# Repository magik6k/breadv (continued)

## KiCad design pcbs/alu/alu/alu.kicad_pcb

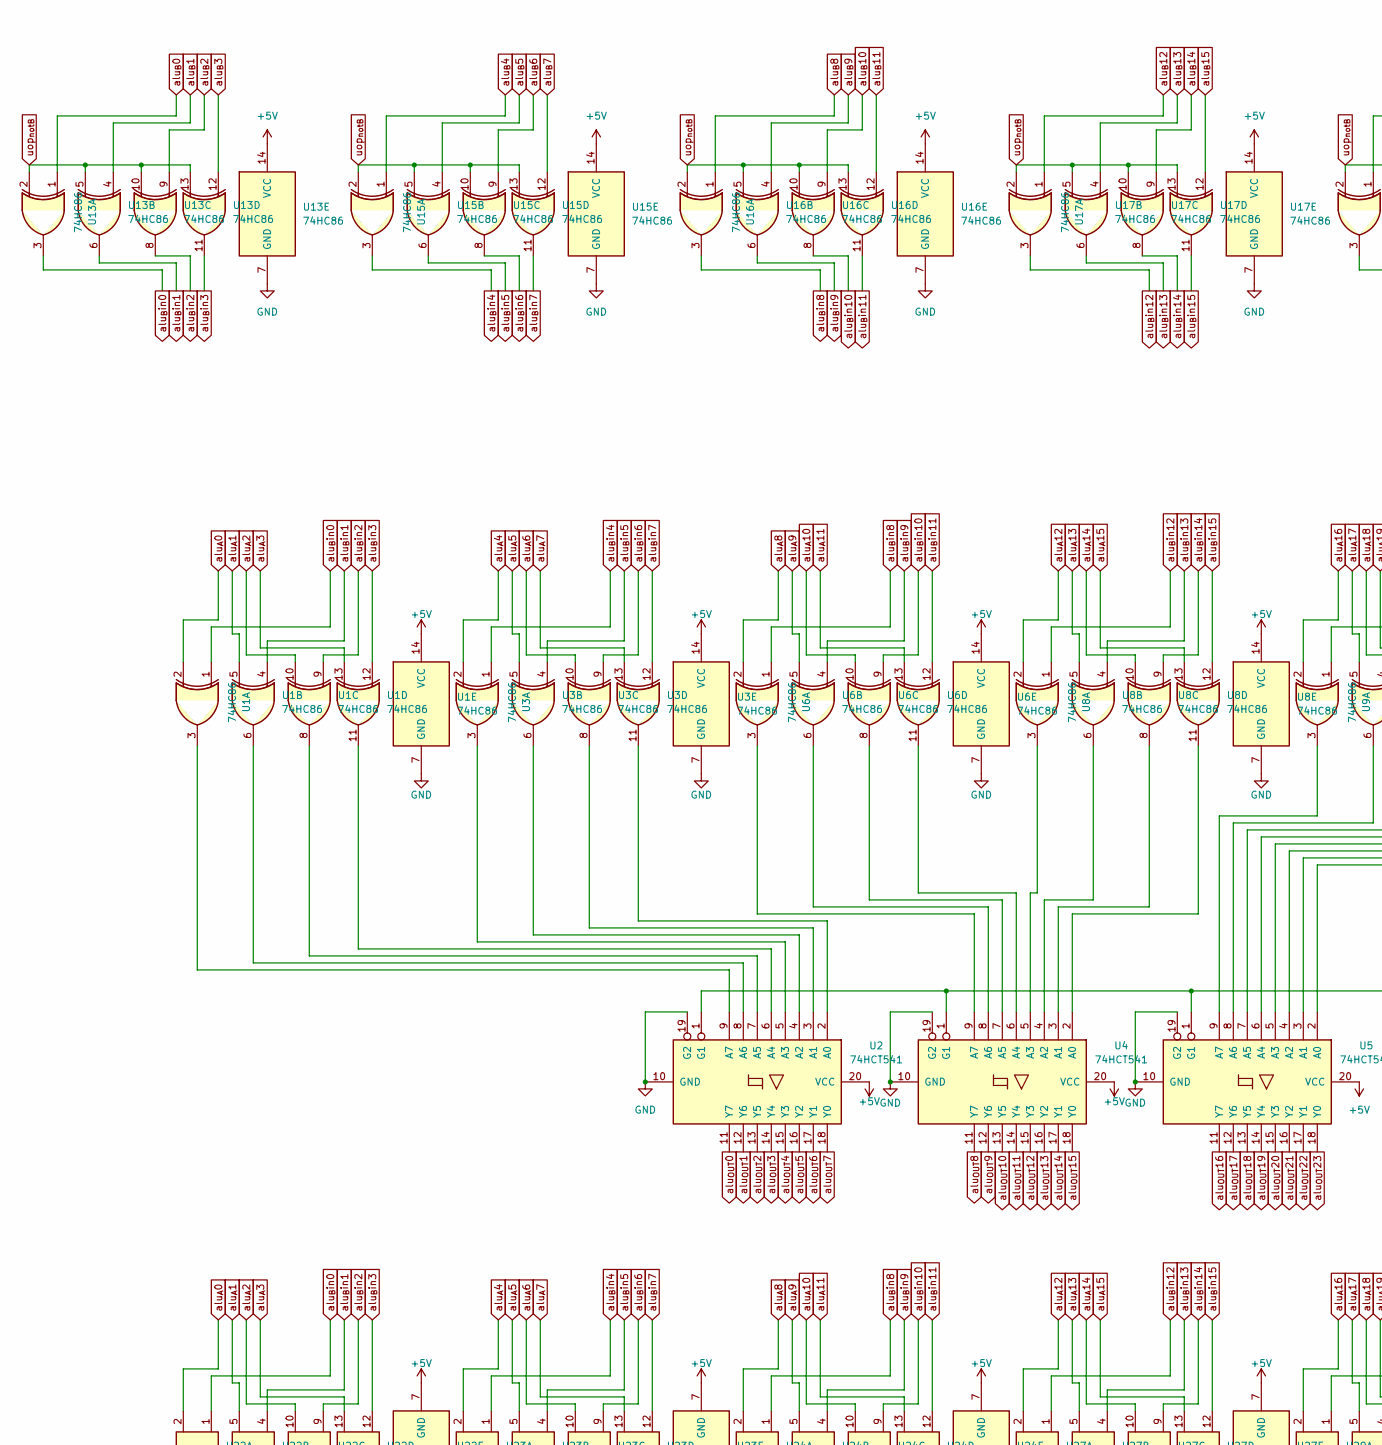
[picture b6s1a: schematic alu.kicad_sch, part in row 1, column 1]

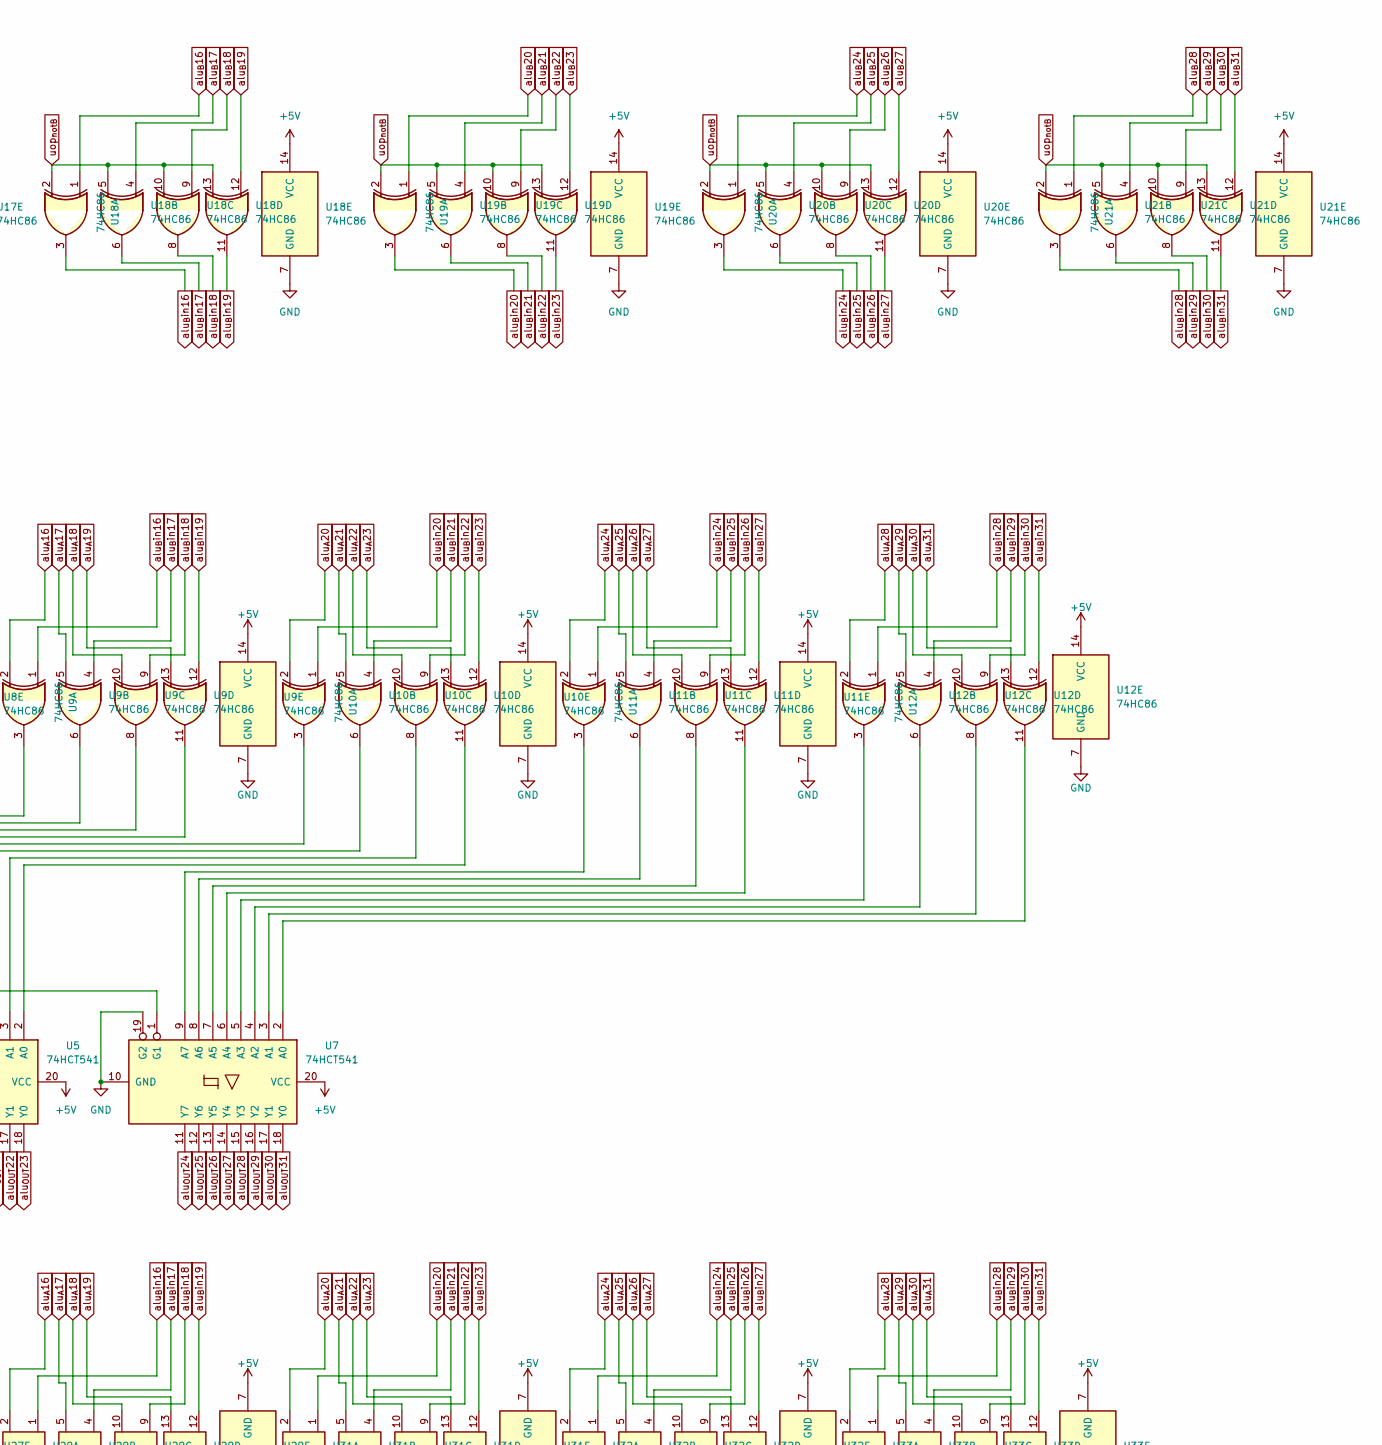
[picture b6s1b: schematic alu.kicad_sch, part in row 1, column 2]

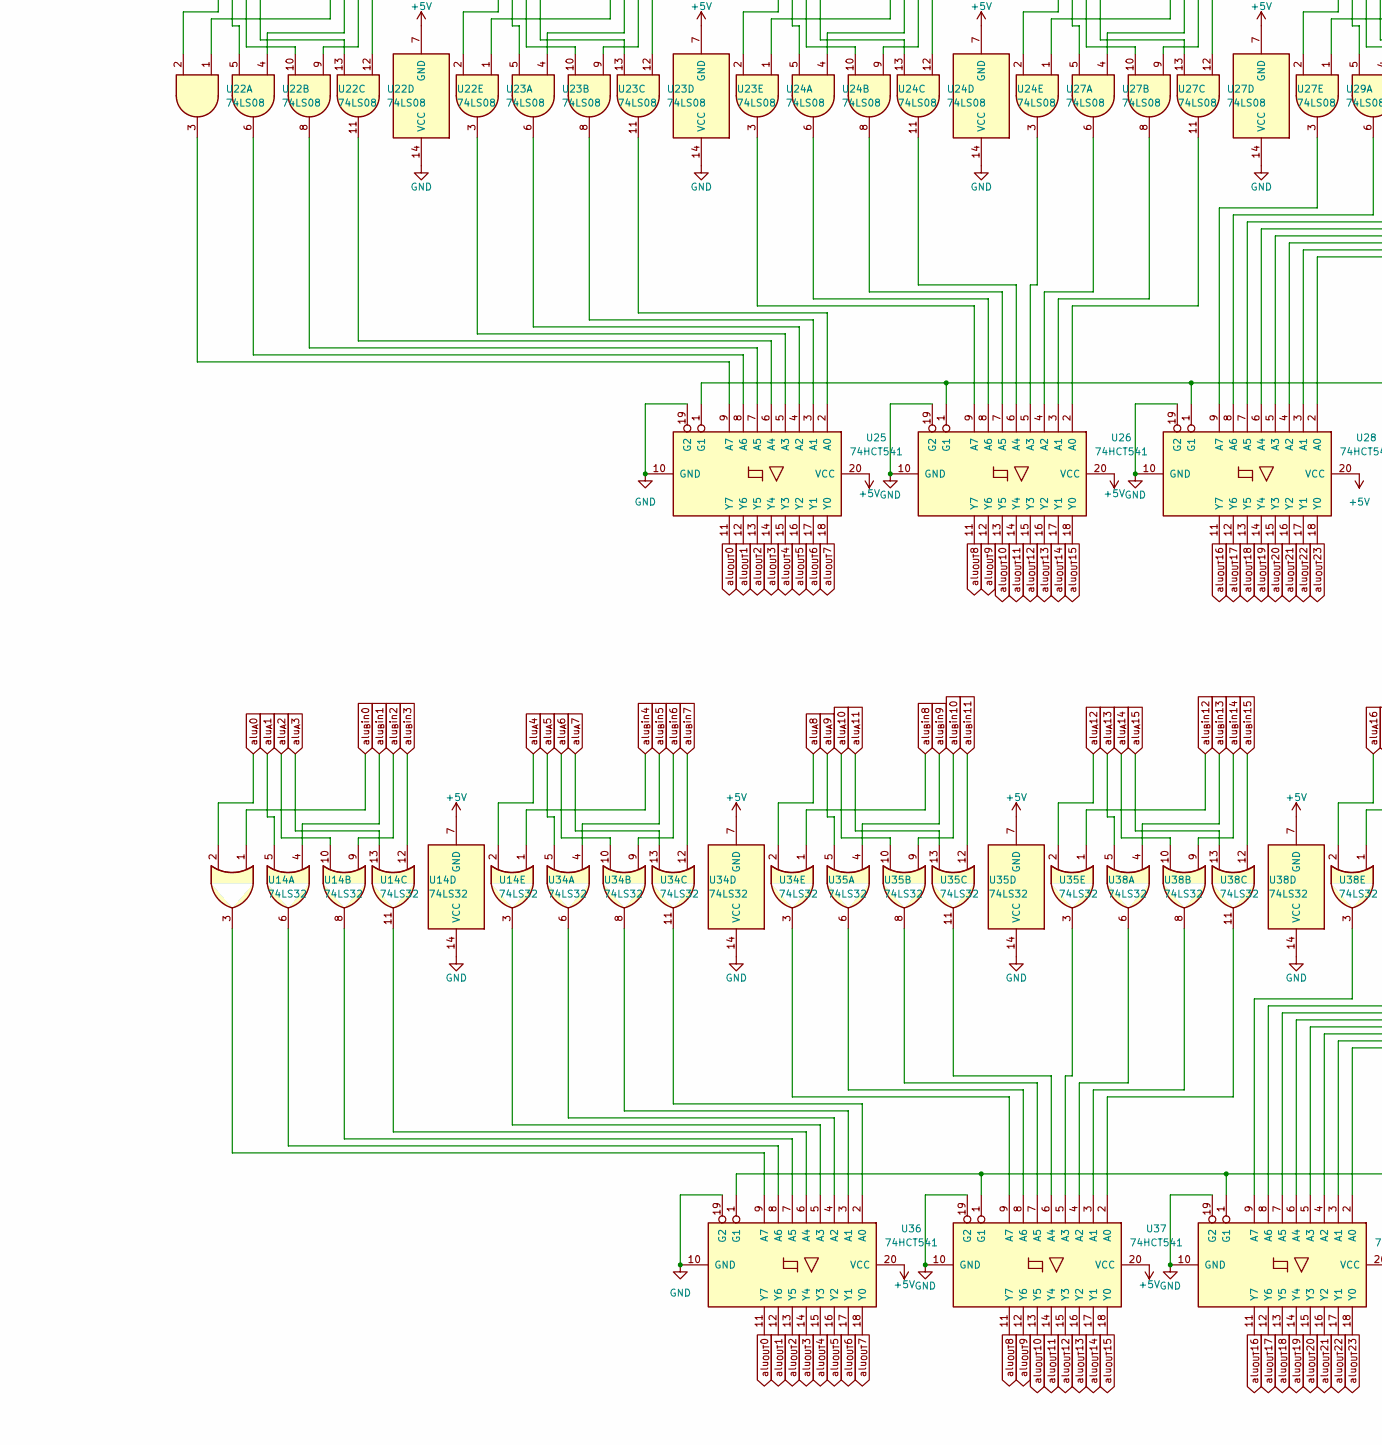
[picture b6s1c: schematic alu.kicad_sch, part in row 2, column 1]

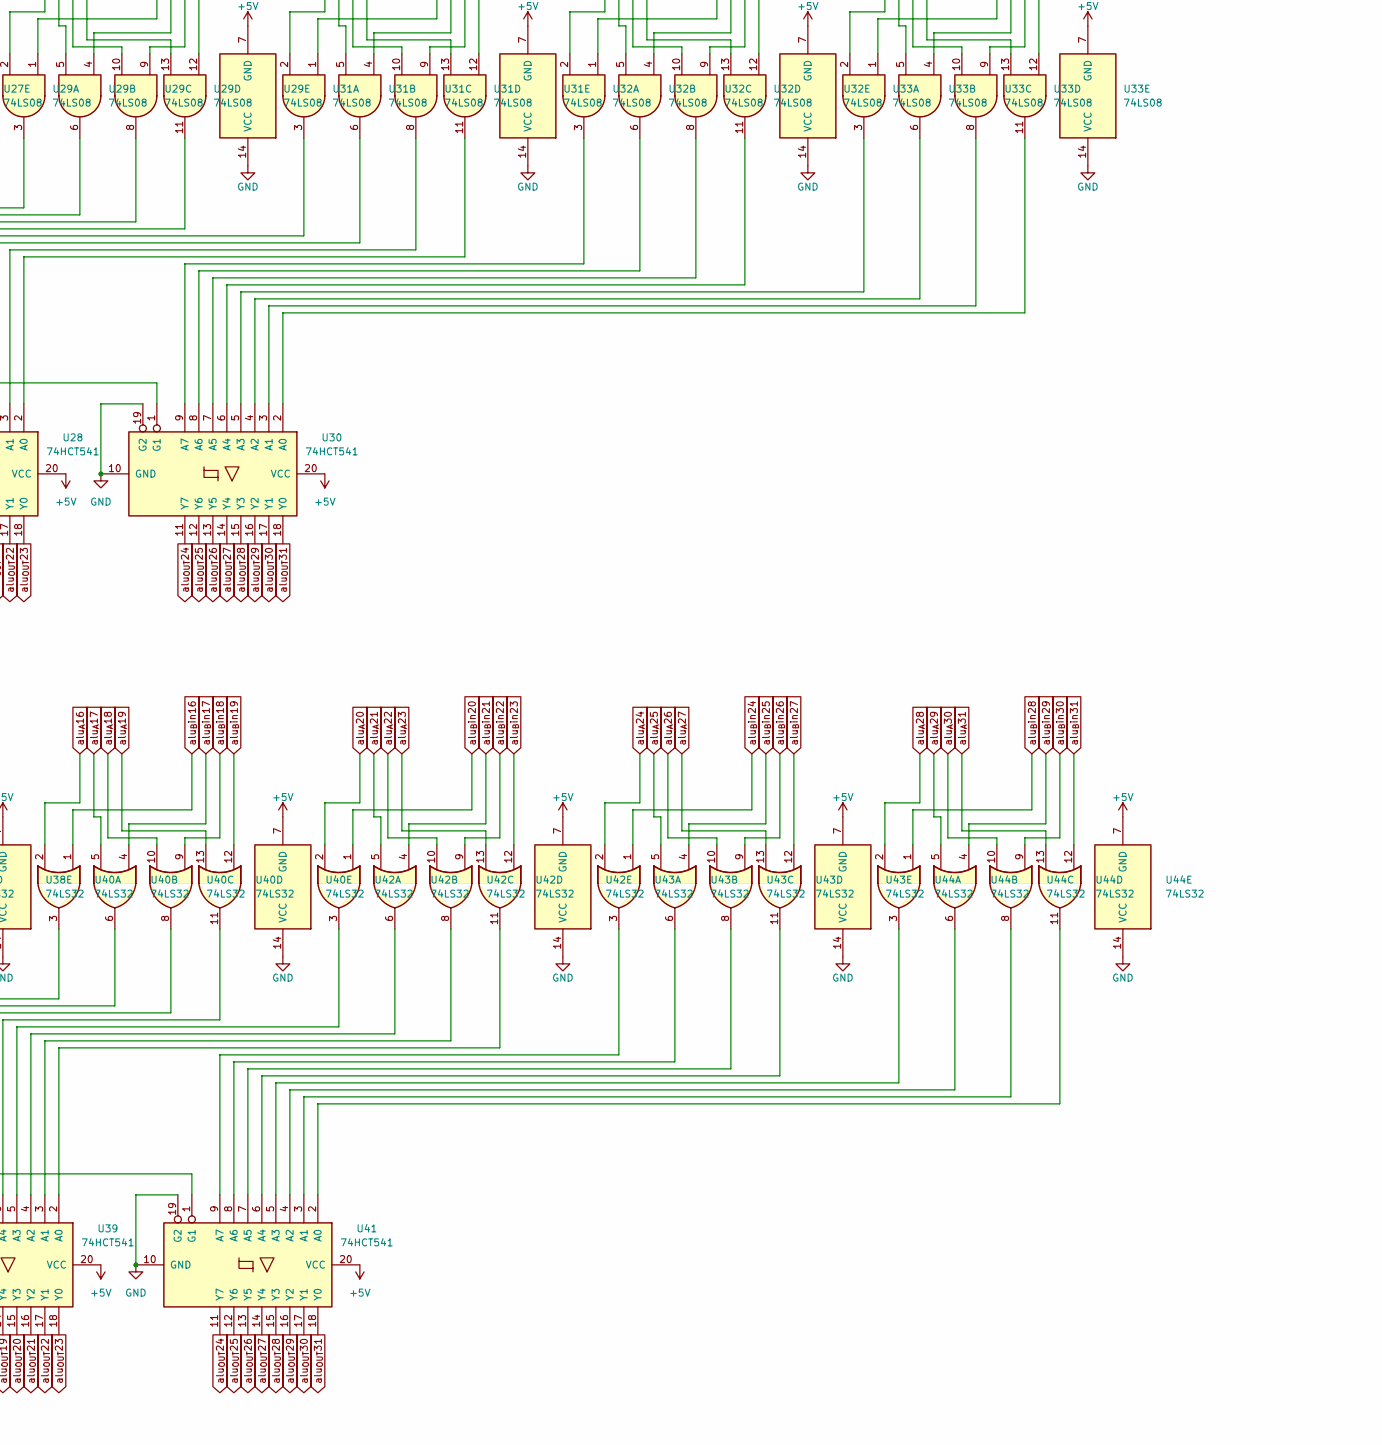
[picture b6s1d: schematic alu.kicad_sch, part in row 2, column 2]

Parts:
U1, U3, U6, U8, U9, U10, U11, U12, U13, U15, U16, U17, U18, U19, U20, U21: 74HC86; DIP-14_W7.62mm_Socket
U2, U4, U5, U7, U25, U26, U28, U30, U36, U37, U39, U41: 74HCT541; DIP-20_W7.62mm_Socket_LongPads
U14, U34, U35, U38, U40, U42, U43, U44: 74LS32; DIP-14_W7.62mm_Socket
U22, U23, U24, U27, U29, U31, U32, U33: 74LS08; DIP-14_W7.62mm_Socket

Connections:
+5V: U1.14 (VCC), U2.20 (VCC), U3.14 (VCC), U4.20 (VCC), U5.20 (VCC), U6.14 (VCC), U7.20 (VCC), U8.14 (VCC), U9.14 (VCC), U10.14 (VCC), U11.14 (VCC), U12.14 (VCC), U13.14 (VCC), U14.7 (GND), U15.14 (VCC), U16.14 (VCC), U17.14 (VCC), U18.14 (VCC), U19.14 (VCC), U20.14 (VCC), U21.14 (VCC), U22.7 (GND), U23.7 (GND), U24.7 (GND), U25.20 (VCC), U26.20 (VCC), U27.7 (GND), U28.20 (VCC), U29.7 (GND), U30.20 (VCC), U31.7 (GND), U32.7 (GND), U33.7 (GND), U34.7 (GND), U35.7 (GND), U36.20 (VCC), U37.20 (VCC), U38.7 (GND), U39.20 (VCC), U40.7 (GND), U41.20 (VCC), U42.7 (GND), U43.7 (GND), U44.7 (GND)
GND: U1.7 (GND), U2.10 (GND), U2.19 (G2), U3.7 (GND), U4.10 (GND), U4.19 (G2), U5.10 (GND), U5.19 (G2), U6.7 (GND), U7.10 (GND), U7.19 (G2), U8.7 (GND), U9.7 (GND), U10.7 (GND), U11.7 (GND), U12.7 (GND), U13.7 (GND), U14.14 (VCC), U15.7 (GND), U16.7 (GND), U17.7 (GND), U18.7 (GND), U19.7 (GND), U20.7 (GND), U21.7 (GND), U22.14 (VCC), U23.14 (VCC), U24.14 (VCC), U25.10 (GND), U25.19 (G2), U26.10 (GND), U26.19 (G2), U27.14 (VCC), U28.10 (GND), U28.19 (G2), U29.14 (VCC), U30.10 (GND), U30.19 (G2), U31.14 (VCC), U32.14 (VCC), U33.14 (VCC), U34.14 (VCC), U35.14 (VCC), U36.10 (GND), U36.19 (G2), U37.10 (GND), U37.19 (G2), U38.14 (VCC), U39.10 (GND), U39.19 (G2), U40.14 (VCC), U41.10 (GND), U41.19 (G2), U42.14 (VCC), U43.14 (VCC), U44.14 (VCC)
unnamed: U1.3, U2.9 (A7)
unnamed: U1.6, U2.8 (A6)
unnamed: U1.8, U2.7 (A5)
unnamed: U1.11, U2.6 (A4)
unnamed: U2.2 (A0), U3.11
unnamed: U2.3 (A1), U3.8
unnamed: U2.4 (A2), U3.6
unnamed: U2.5 (A3), U3.3
unnamed: U4.2 (A0), U8.11
unnamed: U4.3 (A1), U8.8
unnamed: U4.4 (A2), U8.6
unnamed: U4.5 (A3), U8.3
unnamed: U4.6 (A4), U6.11
unnamed: U4.7 (A5), U6.8
unnamed: U4.8 (A6), U6.6
unnamed: U4.9 (A7), U6.3
unnamed: U5.2 (A0), U10.11
unnamed: U5.3 (A1), U10.8
unnamed: U5.4 (A2), U10.6
unnamed: U5.5 (A3), U10.3
unnamed: U5.6 (A4), U9.11
unnamed: U5.7 (A5), U9.8
unnamed: U5.8 (A6), U9.6
unnamed: U5.9 (A7), U9.3
unnamed: U2.1 (G1), U4.1 (G1), U5.1 (G1), U7.1 (G1)
unnamed: U7.2 (A0), U12.11
unnamed: U7.3 (A1), U12.8
unnamed: U7.4 (A2), U12.6
unnamed: U7.5 (A3), U12.3
unnamed: U7.6 (A4), U11.11
unnamed: U7.7 (A5), U11.8
unnamed: U7.8 (A6), U11.6
unnamed: U7.9 (A7), U11.3
unnamed: U14.3, U36.9 (A7)
unnamed: U14.6, U36.8 (A6)
unnamed: U14.8, U36.7 (A5)
unnamed: U14.11, U36.6 (A4)
unnamed: U22.3, U25.9 (A7)
unnamed: U22.6, U25.8 (A6)
unnamed: U22.8, U25.7 (A5)
unnamed: U22.11, U25.6 (A4)
unnamed: U23.3, U25.5 (A3)
unnamed: U23.6, U25.4 (A2)
unnamed: U23.8, U25.3 (A1)
unnamed: U23.11, U25.2 (A0)
unnamed: U24.3, U26.9 (A7)
unnamed: U24.6, U26.8 (A6)
unnamed: U24.8, U26.7 (A5)
unnamed: U24.11, U26.6 (A4)
unnamed: U25.1 (G1), U26.1 (G1), U28.1 (G1), U30.1 (G1)
unnamed: U26.2 (A0), U27.11
unnamed: U26.3 (A1), U27.8
unnamed: U26.4 (A2), U27.6
unnamed: U26.5 (A3), U27.3
unnamed: U28.2 (A0), U31.11
unnamed: U28.3 (A1), U31.8
unnamed: U28.4 (A2), U31.6
unnamed: U28.5 (A3), U31.3
unnamed: U28.6 (A4), U29.11
unnamed: U28.7 (A5), U29.8
unnamed: U28.8 (A6), U29.6
unnamed: U28.9 (A7), U29.3
unnamed: U30.2 (A0), U33.11
unnamed: U30.3 (A1), U33.8
unnamed: U30.4 (A2), U33.6
unnamed: U30.5 (A3), U33.3
unnamed: U30.6 (A4), U32.11
unnamed: U30.7 (A5), U32.8
unnamed: U30.8 (A6), U32.6
unnamed: U30.9 (A7), U32.3
unnamed: U34.3, U36.5 (A3)
unnamed: U34.6, U36.4 (A2)
unnamed: U34.8, U36.3 (A1)
unnamed: U34.11, U36.2 (A0)
unnamed: U35.3, U37.9 (A7)
unnamed: U35.6, U37.8 (A6)
unnamed: U35.8, U37.7 (A5)
unnamed: U35.11, U37.6 (A4)
unnamed: U36.1 (G1), U37.1 (G1), U39.1 (G1), U41.1 (G1)
unnamed: U37.2 (A0), U38.11
unnamed: U37.3 (A1), U38.8
unnamed: U37.4 (A2), U38.6
unnamed: U37.5 (A3), U38.3
unnamed: U39.2 (A0), U42.11
unnamed: U39.3 (A1), U42.8
unnamed: U39.4 (A2), U42.6
unnamed: U39.5 (A3), U42.3
unnamed: U39.6 (A4), U40.11
unnamed: U39.7 (A5), U40.8
unnamed: U39.8 (A6), U40.6
unnamed: U39.9 (A7), U40.3
unnamed: U41.2 (A0), U44.11
unnamed: U41.3 (A1), U44.8
unnamed: U41.4 (A2), U44.6
unnamed: U41.5 (A3), U44.3
unnamed: U41.6 (A4), U43.11
unnamed: U41.7 (A5), U43.8
unnamed: U41.8 (A6), U43.6
unnamed: U41.9 (A7), U43.3
alu_{A}0: U1.2, U14.2, U22.2
alu_{A}1: U1.5, U14.5, U22.5
alu_{A}2: U1.10, U14.10, U22.10
alu_{A}3: U1.13, U14.13, U22.13
alu_{A}4: U3.2, U23.2, U34.2
alu_{A}5: U3.5, U23.5, U34.5
alu_{A}6: U3.10, U23.10, U34.10
alu_{A}7: U3.13, U23.13, U34.13
alu_{A}8: U6.2, U24.2, U35.2
alu_{A}9: U6.5, U24.5, U35.5
alu_{A}10: U6.10, U24.10, U35.10
alu_{A}11: U6.13, U24.13, U35.13
alu_{A}12: U8.2, U27.2, U38.2
alu_{A}13: U8.5, U27.5, U38.5
alu_{A}14: U8.10, U27.10, U38.10
alu_{A}15: U8.13, U27.13, U38.13
alu_{A}16: U9.2, U29.2, U40.2
alu_{A}17: U9.5, U29.5, U40.5
alu_{A}18: U9.10, U29.10, U40.10
alu_{A}19: U9.13, U29.13, U40.13
alu_{A}20: U10.2, U31.2, U42.2
alu_{A}21: U10.5, U31.5, U42.5
alu_{A}22: U10.10, U31.10, U42.10
alu_{A}23: U10.13, U31.13, U42.13
alu_{A}24: U11.2, U32.2, U43.2
alu_{A}25: U11.5, U32.5, U43.5
alu_{A}26: U11.10, U32.10, U43.10
alu_{A}27: U11.13, U32.13, U43.13
alu_{A}28: U12.2, U33.2, U44.2
alu_{A}29: U12.5, U33.5, U44.5
alu_{A}30: U12.10, U33.10, U44.10
alu_{A}31: U12.13, U33.13, U44.13
alu_{B}0: U13.1
alu_{B}1: U13.4
alu_{B}2: U13.9
alu_{B}3: U13.12
alu_{B}4: U15.1
alu_{B}5: U15.4
alu_{B}6: U15.9
alu_{B}7: U15.12
alu_{B}8: U16.1
alu_{B}9: U16.4
alu_{B}10: U16.9
alu_{B}11: U16.12
alu_{B}12: U17.1
alu_{B}13: U17.4
alu_{B}14: U17.9
alu_{B}15: U17.12
alu_{B}16: U18.1
alu_{B}17: U18.4
alu_{B}18: U18.9
alu_{B}19: U18.12
alu_{B}20: U19.1
alu_{B}21: U19.4
alu_{B}22: U19.9
alu_{B}23: U19.12
alu_{B}24: U20.1
alu_{B}25: U20.4
alu_{B}26: U20.9
alu_{B}27: U20.12
alu_{B}28: U21.1
alu_{B}29: U21.4
alu_{B}30: U21.9
alu_{B}31: U21.12
alu_{B}in0: U1.1, U13.3, U14.1, U22.1
alu_{B}in1: U1.4, U13.6, U14.4, U22.4
alu_{B}in2: U1.9, U13.8, U14.9, U22.9
alu_{B}in3: U1.12, U13.11, U14.12, U22.12
alu_{B}in4: U3.1, U15.3, U23.1, U34.1
alu_{B}in5: U3.4, U15.6, U23.4, U34.4
alu_{B}in6: U3.9, U15.8, U23.9, U34.9
alu_{B}in7: U3.12, U15.11, U23.12, U34.12
alu_{B}in8: U6.1, U16.3, U24.1, U35.1
alu_{B}in9: U6.4, U16.6, U24.4, U35.4
alu_{B}in10: U6.9, U16.8, U24.9, U35.9
alu_{B}in11: U6.12, U16.11, U24.12, U35.12
alu_{B}in12: U8.1, U17.3, U27.1, U38.1
alu_{B}in13: U8.4, U17.6, U27.4, U38.4
alu_{B}in14: U8.9, U17.8, U27.9, U38.9
alu_{B}in15: U8.12, U17.11, U27.12, U38.12
alu_{B}in16: U9.1, U18.3, U29.1, U40.1
alu_{B}in17: U9.4, U18.6, U29.4, U40.4
alu_{B}in18: U9.9, U18.8, U29.9, U40.9
alu_{B}in19: U9.12, U18.11, U29.12, U40.12
alu_{B}in20: U10.1, U19.3, U31.1, U42.1
alu_{B}in21: U10.4, U19.6, U31.4, U42.4
alu_{B}in22: U10.9, U19.8, U31.9, U42.9
alu_{B}in23: U10.12, U19.11, U31.12, U42.12
alu_{B}in24: U11.1, U20.3, U32.1, U43.1
alu_{B}in25: U11.4, U20.6, U32.4, U43.4
alu_{B}in26: U11.9, U20.8, U32.9, U43.9
alu_{B}in27: U11.12, U20.11, U32.12, U43.12
alu_{B}in28: U12.1, U21.3, U33.1, U44.1
alu_{B}in29: U12.4, U21.6, U33.4, U44.4
alu_{B}in30: U12.9, U21.8, U33.9, U44.9
alu_{B}in31: U12.12, U21.11, U33.12, U44.12
alu_{OUT}0: U2.11 (Y7), U25.11 (Y7), U36.11 (Y7)
alu_{OUT}1: U2.12 (Y6), U25.12 (Y6), U36.12 (Y6)
alu_{OUT}2: U2.13 (Y5), U25.13 (Y5), U36.13 (Y5)
alu_{OUT}3: U2.14 (Y4), U25.14 (Y4), U36.14 (Y4)
alu_{OUT}4: U2.15 (Y3), U25.15 (Y3), U36.15 (Y3)
alu_{OUT}5: U2.16 (Y2), U25.16 (Y2), U36.16 (Y2)
alu_{OUT}6: U2.17 (Y1), U25.17 (Y1), U36.17 (Y1)
alu_{OUT}7: U2.18 (Y0), U25.18 (Y0), U36.18 (Y0)
alu_{OUT}8: U4.11 (Y7), U26.11 (Y7), U37.11 (Y7)
alu_{OUT}9: U4.12 (Y6), U26.12 (Y6), U37.12 (Y6)
alu_{OUT}10: U4.13 (Y5), U26.13 (Y5), U37.13 (Y5)
alu_{OUT}11: U4.14 (Y4), U26.14 (Y4), U37.14 (Y4)
alu_{OUT}12: U4.15 (Y3), U26.15 (Y3), U37.15 (Y3)
alu_{OUT}13: U4.16 (Y2), U26.16 (Y2), U37.16 (Y2)
alu_{OUT}14: U4.17 (Y1), U26.17 (Y1), U37.17 (Y1)
alu_{OUT}15: U4.18 (Y0), U26.18 (Y0), U37.18 (Y0)
alu_{OUT}16: U5.11 (Y7), U28.11 (Y7), U39.11 (Y7)
alu_{OUT}17: U5.12 (Y6), U28.12 (Y6), U39.12 (Y6)
alu_{OUT}18: U5.13 (Y5), U28.13 (Y5), U39.13 (Y5)
alu_{OUT}19: U5.14 (Y4), U28.14 (Y4), U39.14 (Y4)
alu_{OUT}20: U5.15 (Y3), U28.15 (Y3), U39.15 (Y3)
alu_{OUT}21: U5.16 (Y2), U28.16 (Y2), U39.16 (Y2)
alu_{OUT}22: U5.17 (Y1), U28.17 (Y1), U39.17 (Y1)
alu_{OUT}23: U5.18 (Y0), U28.18 (Y0), U39.18 (Y0)
alu_{OUT}24: U7.11 (Y7), U30.11 (Y7), U41.11 (Y7)
alu_{OUT}25: U7.12 (Y6), U30.12 (Y6), U41.12 (Y6)
alu_{OUT}26: U7.13 (Y5), U30.13 (Y5), U41.13 (Y5)
alu_{OUT}27: U7.14 (Y4), U30.14 (Y4), U41.14 (Y4)
alu_{OUT}28: U7.15 (Y3), U30.15 (Y3), U41.15 (Y3)
alu_{OUT}29: U7.16 (Y2), U30.16 (Y2), U41.16 (Y2)
alu_{OUT}30: U7.17 (Y1), U30.17 (Y1), U41.17 (Y1)
alu_{OUT}31: U7.18 (Y0), U30.18 (Y0), U41.18 (Y0)
uop_{notB}: U13.2, U13.5, U13.10, U13.13, U15.2, U15.5, U15.10, U15.13, U16.2, U16.5, U16.10, U16.13, U17.2, U17.5, U17.10, U17.13, U18.2, U18.5, U18.10, U18.13, U19.2, U19.5, U19.10, U19.13, U20.2, U20.5, U20.10, U20.13, U21.2, U21.5, U21.10, U21.13

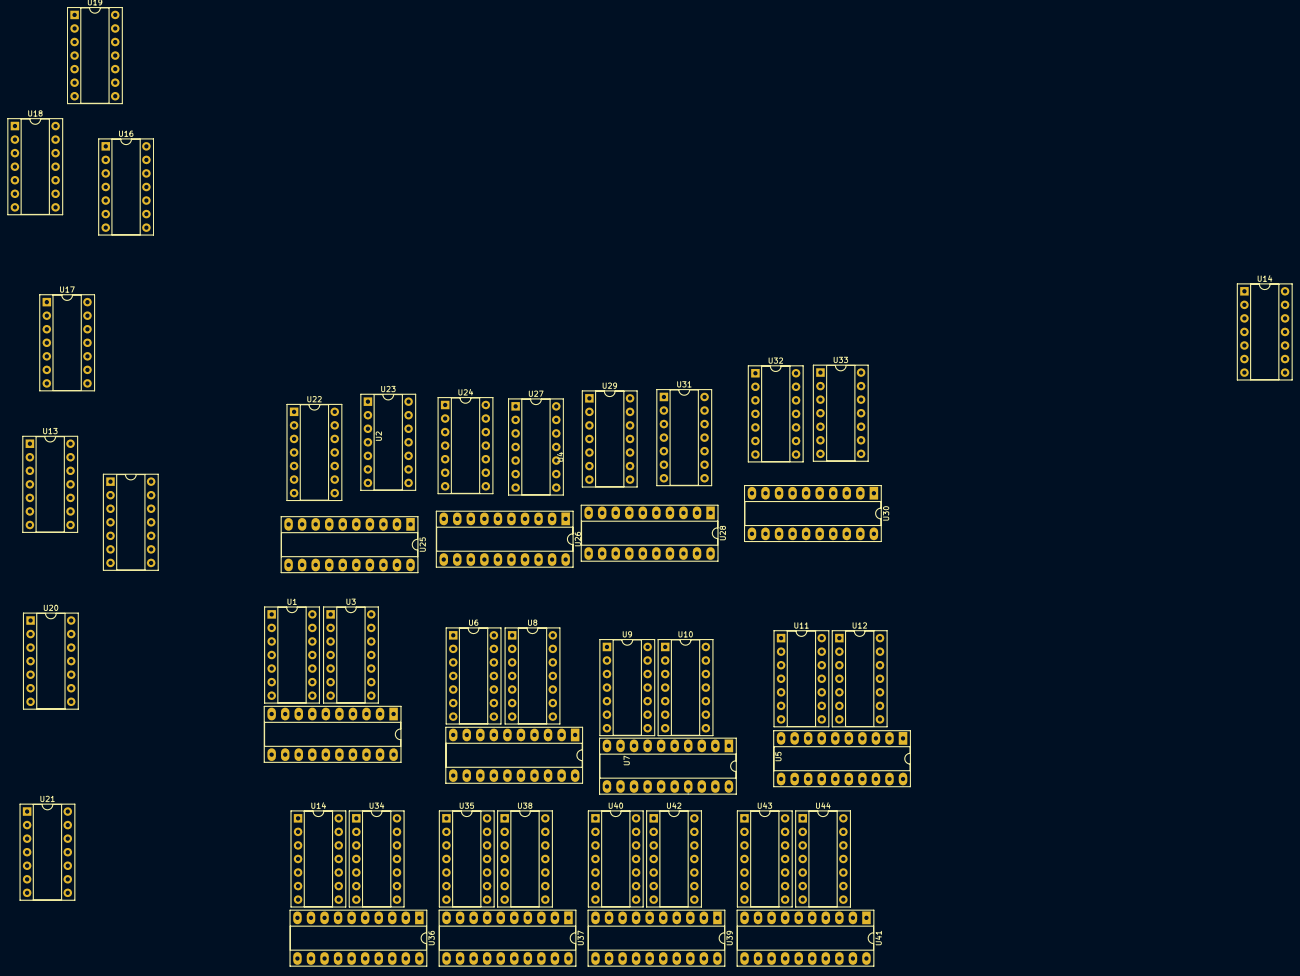
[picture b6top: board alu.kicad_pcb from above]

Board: 2 copper layers, 45 parts (0 on the bottom side), 198 nets.

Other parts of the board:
U14#2: 74LS08; DIP-14_W7.62mm_Socket

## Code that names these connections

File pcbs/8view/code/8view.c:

#include<avr/io.h>
#include<avr/wdt.h>

#define INVERTED 1 // output upside down

#define FILPPED 0 // displays upside down

/*

*A*
F*B
*G*
E*C
*D* DP

*/

#define D1_l1 (1<<PA0)
#define D1_l6 (1<<PA1)
#define D1_l2 (1<<PA2)
#define D1_l7 (1<<PA3)
#define D1_l3 (1<<PA4)
#define D1_l5 (1<<PA5)
#define D1_l8 (1<<PA6)
#define D1_l4 (1<<PA7)

#define D2_l7 (1<<PB0)
#define D2_l8 (1<<PB1)
#define D2_l5 (1<<PB2)
#define D2_l4 (1<<PB3)
#define D2_l6 (1<<PB4)
#define D2_l3 (1<<PB5)
#define D2_l1 (1<<PB6)
#define D2_l2 (1<<PB7)

#if FILPPED
#define D1_real_A D1_l4
#define D1_real_B D1_l5
#define D1_real_C D1_l7
#define D1_real_D D1_l1
#define D1_real_E D1_l2
#define D1_real_F D1_l8
#define D1_real_G D1_l3
#define D1_real_DP D1_l6

#define D2_real_A D2_l4
#define D2_real_B D2_l5
#define D2_real_C D2_l7
#define D2_real_D D2_l1
#define D2_real_E D2_l2
#define D2_real_F D2_l8
#define D2_real_G D2_l3
#define D2_real_DP D2_l6
#else
#define D1_real_A D1_l1
#define D1_real_B D1_l2
#define D1_real_C D1_l3
#define D1_real_D D1_l4
#define D1_real_E D1_l5
#define D1_real_F D1_l6
#define D1_real_G D1_l7
#define D1_real_DP D1_l8

#define D2_real_A D2_l1
#define D2_real_B D2_l2
#define D2_real_C D2_l3
#define D2_real_D D2_l4
#define D2_real_E D2_l5
#define D2_real_F D2_l6
#define D2_real_G D2_l7
#define D2_real_DP D2_l8
#endif

#if INVERTED
#define D1_A D1_real_D
#define D1_B D1_real_E
#define D1_C D1_real_F
#define D1_D D1_real_A
#define D1_E D1_real_B
#define D1_F D1_real_C
#define D1_G D1_real_G
#define D1_DP D1_real_DP

#define D2_A D2_real_D
#define D2_B D2_real_E
#define D2_C D2_real_F
#define D2_D D2_real_A
#define D2_E D2_real_B
#define D2_F D2_real_C
#define D2_G D2_real_G
#define D2_DP D2_real_DP
#else
#define D1_A D1_real_A
#define D1_B D1_real_B
#define D1_C D1_real_C
#define D1_D D1_real_D
#define D1_E D1_real_E
#define D1_F D1_real_F
#define D1_G D1_real_G
#define D1_DP D1_real_DP

#define D2_A D2_real_A
#define D2_B D2_real_B
#define D2_C D2_real_C
#define D2_D D2_real_D
#define D2_E D2_real_E
#define D2_F D2_real_F
#define D2_G D2_real_G
#define D2_DP D2_real_DP
#endif

#define D1_c1 D1_B|D1_C|0
#define D1_c2 D1_A|D1_B|D1_D|D1_E|D1_G|0
#define D1_c3 D1_A|D1_B|D1_C|D1_D|D1_G|0
#define D1_c4 D1_B|D1_C|D1_F|D1_G|0
#define D1_c5 D1_A|D1_C|D1_D|D1_F|D1_G|0
#define D1_c6 D1_A|D1_C|D1_D|D1_E|D1_F|D1_G|0
#define D1_c7 D1_A|D1_B|D1_C|0
#define D1_c8 D1_A|D1_B|D1_C|D1_D|D1_E|D1_F|D1_G|0
#define D1_c9 D1_A|D1_B|D1_C|D1_D|D1_F|D1_G|0
#define D1_c0 D1_A|D1_B|D1_C|D1_D|D1_E|D1_F|0
#define D1_cA D1_A|D1_B|D1_C|D1_D|D1_E|D1_G|0
#define D1_cB D1_C|D1_D|D1_E|D1_F|D1_G|0
#define D1_cC D1_D|D1_E|D1_G|0
#define D1_cD D1_B|D1_C|D1_D|D1_E|D1_G|0
#define D1_cE D1_A|D1_D|D1_E|D1_F|D1_G|0
#define D1_cF D1_A|D1_E|D1_F|D1_G|0
#define D1_cG D1_A|D1_C|D1_D|D1_E|D1_F|0
#define D1_cH D1_C|D1_E|D1_F|D1_G|0
#define D1_cI D1_A|D1_E|0
#define D1_cJ D1_A|D1_C|D1_D|0
#define D1_cK D1_A|D1_C|D1_E|D1_F|D1_G|0
#define D1_cL D1_D|D1_E|D1_F|0
#define D1_cM D1_A|D1_C|D1_E|D1_G|0
#define D1_cN D1_C|D1_E|D1_G|0
#define D1_cO D1_C|D1_D|D1_E|D1_G|0
#define D1_cP D1_A|D1_B|D1_E|D1_F|D1_G|0
#define D1_cQ D1_A|D1_B|D1_C|D1_F|D1_G|0
#define D1_cR D1_E|D1_G|0
#define D1_cS D1_A|D1_C|D1_D|D1_F|0
#define D1_cT D1_D|D1_E|D1_F|D1_G|0
#define D1_cU D1_C|D1_D|D1_E|0
#define D1_cV D1_B|D1_D|D1_F|0
#define D1_cW D1_B|D1_D|D1_F|D1_G|0
#define D1_cX D1_C|D1_E|0
#define D1_cY D1_B|D1_C|D1_D|D1_F|D1_G|0
#define D1_cZ D1_A|D1_B|D1_D|D1_E|0

#define D2_c1 D2_B|D2_C|0
#define D2_c2 D2_A|D2_B|D2_D|D2_E|D2_G|0
#define D2_c3 D2_A|D2_B|D2_C|D2_D|D2_G|0
#define D2_c4 D2_B|D2_C|D2_F|D2_G|0
#define D2_c5 D2_A|D2_C|D2_D|D2_F|D2_G|0
#define D2_c6 D2_A|D2_C|D2_D|D2_E|D2_F|D2_G|0
#define D2_c7 D2_A|D2_B|D2_C|0
#define D2_c8 D2_A|D2_B|D2_C|D2_D|D2_E|D2_F|D2_G|0
#define D2_c9 D2_A|D2_B|D2_C|D2_D|D2_F|D2_G|0
#define D2_c0 D2_A|D2_B|D2_C|D2_D|D2_E|D2_F|0
#define D2_cA D2_A|D2_B|D2_C|D2_D|D2_E|D2_G|0
#define D2_cB D2_C|D2_D|D2_E|D2_F|D2_G|0
#define D2_cC D2_D|D2_E|D2_G|0
#define D2_cD D2_B|D2_C|D2_D|D2_E|D2_G|0
#define D2_cE D2_A|D2_D|D2_E|D2_F|D2_G|0
#define D2_cF D2_A|D2_E|D2_F|D2_G|0
#define D2_cG D2_A|D2_C|D2_D|D2_E|D2_F|0
#define D2_cH D2_C|D2_E|D2_F|D2_G|0
#define D2_cI D2_A|D2_E|0
#define D2_cJ D2_A|D2_C|D2_D|0
#define D2_cK D2_A|D2_C|D2_E|D2_F|D2_G|0
#define D2_cL D2_D|D2_E|D2_F|0
#define D2_cM D2_A|D2_C|D2_E|D2_G|0
#define D2_cN D2_C|D2_E|D2_G|0
#define D2_cO D2_C|D2_D|D2_E|D2_G|0
#define D2_cP D2_A|D2_B|D2_E|D2_F|D2_G|0
#define D2_cQ D2_A|D2_B|D2_C|D2_F|D2_G|0
#define D2_cR D2_E|D2_G|0
#define D2_cS D2_A|D2_C|D2_D|D2_F|0
#define D2_cT D2_D|D2_E|D2_F|D2_G|0
#define D2_cU D2_C|D2_D|D2_E|0
#define D2_cV D2_B|D2_D|D2_F|0
#define D2_cW D2_B|D2_D|D2_F|D2_G|0
#define D2_cX D2_C|D2_E|0
#define D2_cY D2_B|D2_C|D2_D|D2_F|D2_G|0
#define D2_cZ D2_A|D2_B|D2_D|D2_E|0

#if INVERTED

const uint8_t d1lut[] = {
    D1_c0, // 0000
    D1_c8, // 0001
    D1_c4, // 0010
    D1_cC, // 0011
    D1_c2, // 0100
    D1_cA, // 0101
    D1_c6, // 0110
    D1_cE, // 0111
    D1_c1, // 1000
    D1_c9, // 1001
    D1_c5, // 1010
    D1_cD, // 1011
    D1_c3, // 1100
    D1_cB, // 1101
    D1_c7, // 1110
    D1_cF //  1111
};

const uint8_t d2lut[] = {
    D2_c0,
    D2_c8,
    D2_c4,
    D2_cC,
    D2_c2,
    D2_cA,
    D2_c6,
    D2_cE,
    D2_c1,
    D2_c9,
    D2_c5,
    D2_cD,
    D2_c3,
    D2_cB,
    D2_c7,
    D2_cF
};

#else

const uint8_t d1lut[] = {
    D1_c0, // 0000
    D1_c1, // 0001
    D1_c2, // 0010
    D1_c3, // 0011
    D1_c4, // 0100
    D1_c5, // 0101
    D1_c6, // 0110
    D1_c7, // 0111
    D1_c8, // 1000
    D1_c9, // 1001
    D1_cA, // 1010
    D1_cB, // 1011
    D1_cC, // 1100
    D1_cD, // 1101
    D1_cE, // 1110
    D1_cF //  1111
};

const uint8_t d2lut[] = {
    D2_c0,
    D2_c1,
    D2_c2,
    D2_c3,
    D2_c4,
    D2_c5,
    D2_c6,
    D2_c7,
    D2_c8,
    D2_c9,
    D2_cA,
    D2_cB,
    D2_cC,
    D2_cD,
    D2_cE,
    D2_cF
};

#endif

// <riscv instruction mode>

#define RV_INSTR_MODE 0

// riscv instructions, opcode (bits 6:2) and funct3 (bits 14:12)
#define rLU ((0<<6)|(1<<5)|(1<<4)|(0<<3)|(1<<2)) >> 2 // LUI
#define rAU ((0<<6)|(0<<5)|(1<<4)|(0<<3)|(1<<2)) >> 2 // AUIPC
#define rJL ((1<<6)|(1<<5)|(0<<4)|(1<<3)|(1<<2)) >> 2 // JAL
#define rJR ((1<<6)|(1<<5)|(0<<4)|(0<<3)|(1<<2)) >> 2 // JALR
#define rBR ((1<<6)|(1<<5)|(0<<4)|(0<<3)|(0<<2)) >> 2 // BEQ
#define rLD ((0<<6)|(0<<5)|(0<<4)|(0<<3)|(0<<2)) >> 2 // LB
#define rSD ((0<<6)|(1<<5)|(0<<4)|(0<<3)|(0<<2)) >> 2 // SB
#define rAI ((0<<6)|(0<<5)|(1<<4)|(0<<3)|(0<<2)) >> 2 // ADDI
#define rAR ((0<<6)|(1<<5)|(1<<4)|(0<<3)|(0<<2)) >> 2 // ADD
#define rFE ((0<<6)|(0<<5)|(0<<4)|(1<<3)|(1<<2)) >> 2 // FENCE
#define rEE ((1<<6)|(1<<5)|(1<<4)|(0<<3)|(0<<2)) >> 2 // ECALL
#define rSY ((1<<6)|(1<<5)|(1<<4)|(0<<3)|(0<<2)) >> 2 // EBREAK

const uint8_t rviLutD1[32] = {
    [rLU] = D1_cL,
    [rAU] = D1_cA,
    [rJL] = D1_cJ,
    [rJR] = D1_cJ,
    [rBR] = D1_cB,
    [rLD] = D1_cL,
    [rSD] = D1_cS,
    [rAI] = D1_cA,
    [rAR] = D1_cA,
    [rFE] = D1_cF,
    [rEE] = D1_cE,
    [rSY] = D1_cS
};

// 5 bits of opcode
const uint8_t rviLutD2[32] = {
    [rLU] = D2_cU,
    [rAU] = D2_cU,
    [rJL] = D2_cL,
    [rJR] = D2_cR,
    [rBR] = D2_cR,
    [rLD] = D2_cD,
    [rSD] = D2_cD,
    [rAI] = D2_cI,
    [rAR] = D2_cR,
    [rFE] = D2_cE,
    [rEE] = D2_cE,
    [rSY] = D2_cY
};

#define getbit(i, src, dst) (((i&(1<<src))>>src)<<dst)

void main() {
    DDRB |= 0xff;
    DDRA |= 0xff;
    DDRC |= 0x0;

    PORTA = 0xff;
    PORTB = 0xff;

    while(1) {
            wdt_reset();

            uint8_t val = PINC;

            uint8_t instr = getbit(val, 7, 0) | getbit(val, 6, 1) | getbit(val, 5, 2) | getbit(val, 4, 3) | getbit(val, 3, 4) | getbit(val, 2, 5) | getbit(val, 1, 6);

            #if RV_INSTR_MODE
            // if non zero in lut, use it with D2_DP set, otherwise fallback to default display
            if(rviLutD1[(instr>>2)] && instr&0x3 > 0){
                instr = instr >> 2;
                instr = instr & 0x1f;

                PORTA = ~(rviLutD1[instr]);
                if getbit(val, 0, 7) {
                    PORTA ^= D1_DP;
                }
                PORTB = ~(rviLutD2[instr] | D2_DP);

                continue;
            }

            #endif

            instr |= getbit(val, 0, 7);

            #if INVERTED
            PORTA = ~d1lut[(instr >> 4) & 0xf];
            PORTB = ~d2lut[instr & 0xf];
            #else
            PORTA = ~d1lut[(instr >> 4) & 0xf];
            PORTB = ~d2lut[instr & 0xf];
            #endif

    }
}

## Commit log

2021-10-10 init
2021-10-10 add use_rs decoding to op lut
2021-10-21 Mostly working data path
2021-10-26 SW/JAL(R) progress
2021-10-26 instructor memory load/execute
2021-10-26 independent mode
2021-10-26 license
2021-10-26 hardware asm repl
2021-10-26 fw: move things around
2021-10-26 cable feeder code
2021-10-27 mispredict/store discard
2021-12-18 wip branches
2021-12-19 clock: Use portb
2021-12-28 alu ops work
2021-12-28 gofmt
2021-12-29 load
2021-12-29 CSRRW, mostly
2021-12-29 start running some C code; CSR gpio
2021-12-29 ucode: SLT*
2021-12-30 more wrangling with LOAD
2021-12-30 make load work a little more
2022-01-15 faster max clock speed
2022-01-16 32x32 led register dispaly
2022-01-16 32x32 matrix overlay
2022-01-16 memory debugging
2022-01-16 fix SP setup
2022-01-17 load const test
2022-01-18 fix endiannes
2022-01-19 optimize reg display
2022-01-20 basic hd44780 driver
2022-02-22 Create Sjenica1
    Authorized mit meine Account Sjenica1 github.com reufrujevic750@gmail.com
2022-03-13 cable feeder v2
2022-03-14 alu uops rom
2022-03-14 it shifts
2022-05-29 more test fun
2022-05-29 much more stable, non racy instructor
2022-06-26 messing with stuff
2022-06-26 ucode: New imm decoder ucode
2022-07-02 drop useless boot code
2022-07-02 cleanup instructd
2022-07-02 memory dump support
2022-07-16 ucode: ignore cmp_in in add/sub
2022-07-16 unil for diffing memory
2022-07-16 some test progs
2022-07-17 auipc reg lookahead hwtest
2022-07-17 shell funcs for single exec instructions
2022-11-24 more messing around
2022-11-24 add pcbs
2022-11-25 v1 8view borads
2022-12-03 rom loader
2022-12-03 more rom loader funtimes
2022-12-14 8view code
2022-12-14 rom loader fixes
2022-12-15 8view: 10pin skirt, 1.5k leds
2022-12-15 8view: testpoints
2022-12-15 8view: caps++
2022-12-15 8view: nicer tp labels
2022-12-15 8view: v1.1 touches
2022-12-15 8view: rm c silkscreen
2023-01-03 8view 1.1 code, readme
2023-01-21 8view: inverted mode
2023-01-28 8view: flipped mode
2023-02-25 sort of working iota
2023-02-25 attempts to make instructor faster
2023-02-25 memory bank decoder pcb
2023-04-29 messing with uart
2023-05-27 new uart base..
